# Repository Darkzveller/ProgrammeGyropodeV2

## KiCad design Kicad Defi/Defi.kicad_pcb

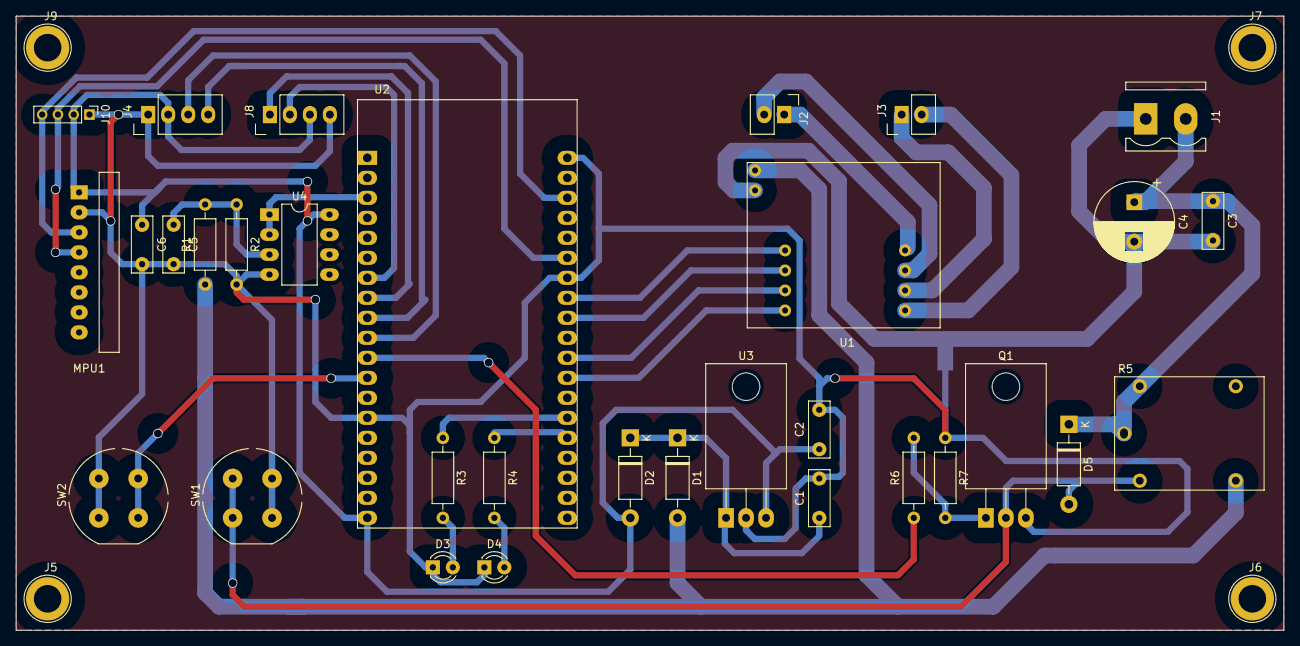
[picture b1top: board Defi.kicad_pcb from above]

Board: 2 copper layers, 161.0 x 78.0 mm, 37 parts (1 on the bottom side), 30 nets.

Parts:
C1, C3, C5, C6: 100n; C_Rect_L7.0mm_W2.5mm_P5.00mm
C2: 330n; C_Rect_L7.0mm_W2.5mm_P5.00mm
C4: 100µ; CP_Radial_D10.0mm_P5.00mm
D1, D2, D5: 1N400X; D_DO-41_SOD81_P10.16mm_Horizontal
D3, D4: LED3mm_orange; LED_D3.0mm_orange
J1: Omnimate2; OmnimateSL-5,08_1x02_P5.08mm_Vertical
J2, J3: Autocom2
J4, J8: Autocom4
J5, J6, J7, J9: Mounting_Screw_3mm
J10: Autocom4; PinHeader_1x04_P2.00mm_Vertical
MPU1: MPU6050
NT4: NetTie_2; NetTie-2_SMD_Pad2.0mm
Q1: IRL510; TO-220-3_Horizontal_TabDown
R1: 15k; R_Axial_DIN0207_L6.3mm_D2.5mm_P10.16mm_Horizontal
R2: 5600; R_Axial_DIN0207_L6.3mm_D2.5mm_P10.16mm_Horizontal
R3, R4: 480; R_Axial_DIN0207_L6.3mm_D2.5mm_P10.16mm_Horizontal
R5: HF3FA
R6: 100; R_Axial_DIN0207_L6.3mm_D2.5mm_P10.16mm_Horizontal
R7: 10k; R_Axial_DIN0207_L6.3mm_D2.5mm_P10.16mm_Horizontal
SW1, SW2: SW_Push_blue; SW_PUSH_5mm_blue
U1: Mini_L298N
U2: ESP32-DEVKITC-32D; MODULE_ESP32-DEVKITC-32D
U3: LM7805_TO220; TO-220-3_Horizontal_TabDown
U4: TL082; DIP-8_W7.62mm_LongPads

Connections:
+5V: C2.1, C6.1, D2.2 (A), J4.2, J8.3, J10.2, MPU1.1 (VCC), U2.19 (EXT_5V), U3.3 (VO), U4.8 (V+)
+12P: D1.2 (A), R1.1, R5.4 (NO), U1.1 (VDD)
+12V: C3.1, C4.1, D5.1 (K), J1.2, R5.1 (C), R5.3 (Com)
Bouton Reset: SW2.2, U2.12 (IO14)
EncodeurA: J8.2, U2.7 (IO32)
EncodeurB: J8.1, U2.8 (IO33)
EncodeurC: J4.4, U2.9 (IO25)
EncodeurD: J4.3, U2.10 (IO26)
GND: C1.2, C2.2, C5.2, C6.2, D3.1 (K), D4.1 (K), J4.1, J8.4, J10.1, MPU1.2 (GND), NT4.2, Q1.3 (S), R2.2, R7.1, SW1.2, SW2.1, U2.14 (GND1), U2.20 (GND3), U2.26 (GND2), U3.2 (GND), U4.4 (V-)
GNDPWR: C3.2, C4.2, J1.1, NT4.1, U1.2 (GND)
Led1: R3.1, U2.33 (IO0)
Led2: R4.1, U2.34 (IO2)
Moteur A: J2.1, U1.7 (Out1_Moteur_A)
Moteur B: J2.2, U1.8 (Out2_Moteur_A)
Moteur C: J3.1, U1.9 (Out1_Moteur_B)
Moteur D: J3.2, U1.10 (Out2_Moteur_B)
unnamed: C1.1, D1.1 (K), D2.1 (K), U3.1 (VI)
unnamed: D3.2 (A), R3.2
unnamed: D4.2 (A), R4.2
unnamed: D5.2 (A), Q1.2 (D), R5.2 (C), SW1.1
unnamed: Q1.1 (G), R6.2, R7.2
unnamed: C5.1, R1.2, R2.1, U4.3 (+)
PWM_1: U1.6 (IN4), U2.31 (IO16)
PWM_2: U1.5 (IN3), U2.30 (IO17)
PWM_3: U1.4 (IN2), U2.28 (IO18)
PWM_4: U1.3 (IN1), U2.27 (IO19)
SCL: J10.4, MPU1.3 (SCL), U2.22 (IO22)
SDA: J10.3, MPU1.4 (SDA), U2.25 (IO21)
Signal de commande: R6.1, U2.11 (IO27)
Tension: U2.3 (SENSOR_VP), U4.1, U4.2 (-)

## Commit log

2024-11-21 premier commit
2024-11-21 Mutex + LCD+ENCODEUR+MPU = test validé
2024-11-21 Mise en place de la tache + LED + DEF SCAN I2C ID + AFFICHAGE INIT + Commentaire précédent test toujours présent
2024-11-21 Retirer commentaire code précédent, mais code principale aucun changement pour l'instant
2025-05-09 Je sais plus ce que j'ai fait mais j'envoie au cas ou
2025-11-21 Ajout pin moteur et fonctionnement moteur
2025-11-21 Ajout meusre tension fonctionnelle
2025-11-21 Ajout interrupteur batterie + ajout kp kd Ki en position et premier réglages des coeffs
2025-11-21 Ajout de toute la partie asservissement vitesse + il faut redéterminer les différents coefficient permettant au robot de pouvoir s'asservir + ajout de la config terminal mecatro + ajout code joshua
